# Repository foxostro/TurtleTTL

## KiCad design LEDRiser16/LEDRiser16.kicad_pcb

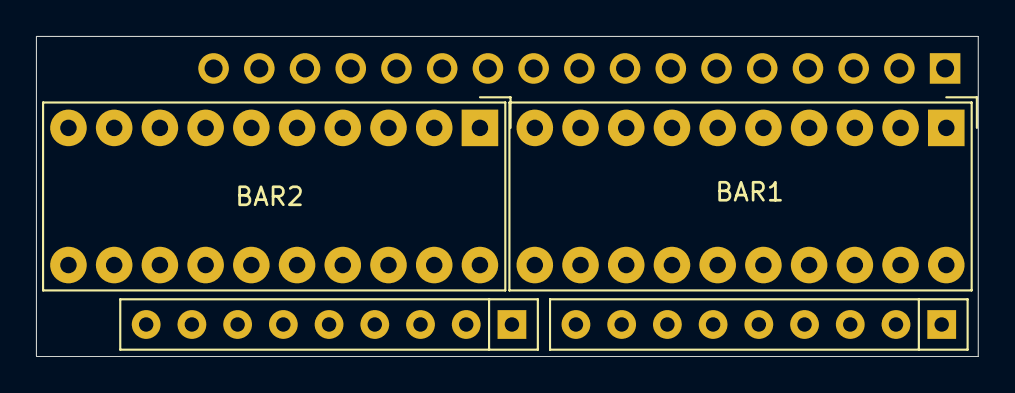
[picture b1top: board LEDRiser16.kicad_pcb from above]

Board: 2 copper layers, 52.3 x 17.8 mm, 5 parts (1 on the bottom side), 33 nets, no tracks yet.

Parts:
BAR1, BAR2: HDSP-4830_2; HDSP-4830
J1: Conn_01x17_Male; PinHeader_1x17_P2.54mm_Vertical
RN1, RN2: 10kΩ; R_Array_SIP9

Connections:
GND: J1.17, RN1.1, RN2.1
unnamed: BAR1.1, J1.1
unnamed: BAR1.2, J1.2
unnamed: BAR1.3, J1.3
unnamed: BAR1.4, J1.4
unnamed: BAR1.5, J1.5
unnamed: BAR1.6, J1.6
unnamed: BAR1.7, J1.7
unnamed: BAR1.8, J1.8
unnamed: BAR1.9, J1.9
unnamed: BAR1.10, J1.10
unnamed: BAR1.11, RN2.3
unnamed: BAR1.12, RN2.2
unnamed: BAR1.13, RN1.9
unnamed: BAR1.14, RN1.8
unnamed: BAR1.15, RN1.7
unnamed: BAR1.16, RN1.6
unnamed: BAR1.17, RN1.5
unnamed: BAR1.18, RN1.4
unnamed: BAR1.19, RN1.3
unnamed: BAR1.20, RN1.2
unnamed: BAR2.1, J1.11
unnamed: BAR2.2, J1.12
unnamed: BAR2.3, J1.13
unnamed: BAR2.4, J1.14
unnamed: BAR2.5, J1.15
unnamed: BAR2.6, J1.16
unnamed: BAR2.15, RN2.9
unnamed: BAR2.16, RN2.8
unnamed: BAR2.17, RN2.7
unnamed: BAR2.18, RN2.6
unnamed: BAR2.19, RN2.5
unnamed: BAR2.20, RN2.4

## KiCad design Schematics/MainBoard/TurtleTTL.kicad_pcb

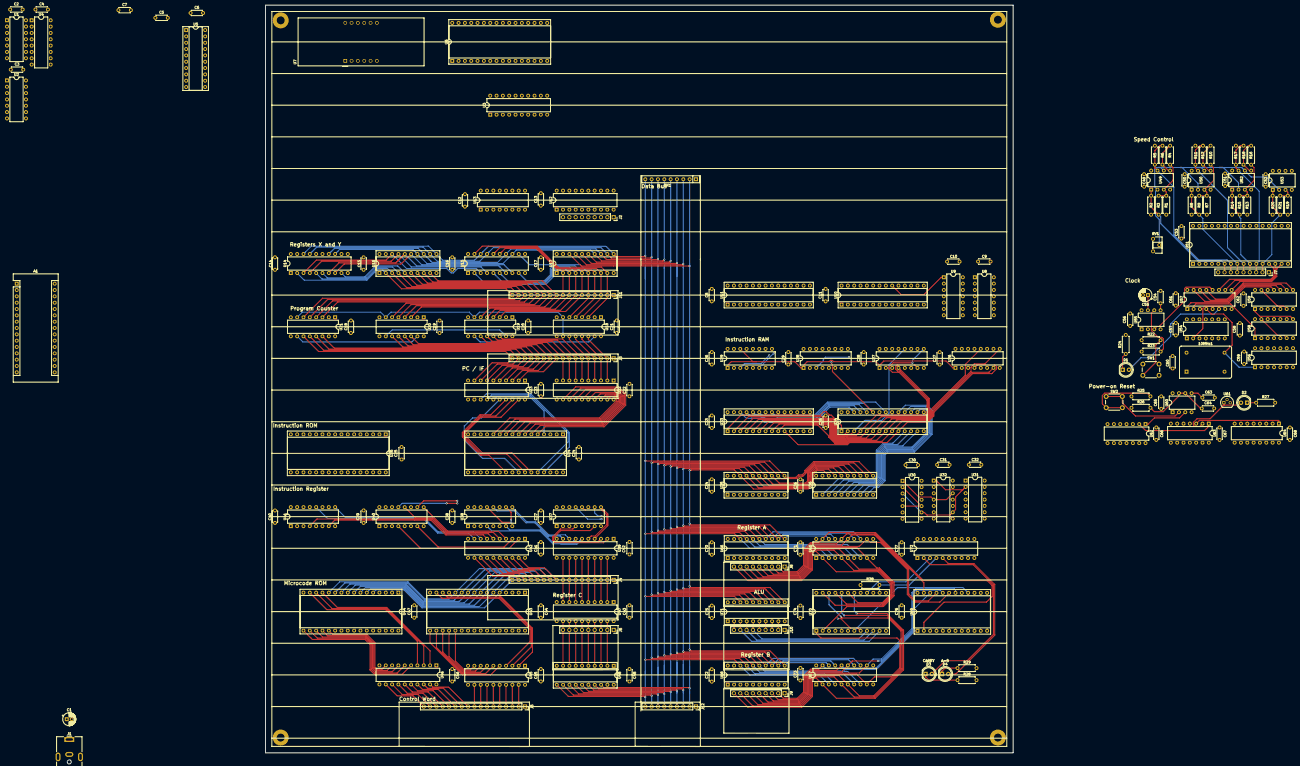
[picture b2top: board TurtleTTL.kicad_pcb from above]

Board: 6 copper layers, 300.0 x 300.0 mm, 204 parts (0 on the bottom side), 305 nets.

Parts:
10MHz1: ACO-xxxMHz; Oscillator_DIP-14
A1: Arduino_Nano_v3.x; Arduino_Nano
C1, C55: 10µF; CP_Radial_D5.0mm_P2.00mm
C2, C3, C4, C5, C6, C7, C8, C9, C10, C11, C12, C13, C14, C15, C16, C17, C18, C19, C20, C21, C22, C23, C24, C25, C26, C27, C28, C29, C30, C31, C32, C33, C34, C35, C36, C37, C38, C39, C40, C41, C42, C43, C44, C45, C46, C47, C48, C49, C50, C51, C52, C53, C56, C57, C58, C59, C60, C61, C62, C64, C65, C66, C67, C68, C70, C71, C72, C73, C74, C75, C76, C77: 100nF; C_Disc_D4.3mm_W1.9mm_P5.00mm
C54, C63: 10nF; C_Disc_D4.3mm_W1.9mm_P5.00mm
D1, D2, D3, D4: LED; LED_D5.0mm
J1: Barrel_Jack; BarrelJack_CUI_PJ-063AH_Horizontal
J2: Device Select LED Connector; PinSocket_1x09_P2.54mm_Vertical
J3: Program Counter LED Connector; PinSocket_1x17_P2.54mm_Vertical
J4: Instruction Register LED Connector; PinSocket_1x17_P2.54mm_Vertical
J5: C Register LED Connector; PinSocket_1x09_P2.54mm_Vertical
J6: Control Word LED Connector; PinSocket_1x17_P2.54mm_Vertical
J7: Speed Control LED Connector; PinSocket_1x09_P2.54mm_Vertical
J8: A Register LED Connector; PinSocket_1x09_P2.54mm_Vertical
J9: B Register LED Connector; PinSocket_1x09_P2.54mm_Vertical
J10: ALU Result LED Connector; PinSocket_1x09_P2.54mm_Vertical
J11: Address Bus LED Connector; PinSocket_1x17_P2.54mm_Vertical
J12: Data Bus LED Connector; PinSocket_1x09_P2.54mm_Vertical
MOUNT_LL: MountingHole_3.2mm_M3_Pad
MOUNT_LR: MountingHole_3.2mm_M3_Pad
MOUNT_UL: MountingHole_3.2mm_M3_Pad
MOUNT_UR: MountingHole_3.2mm_M3_Pad
R1, R2, R4, R5, R7, R8, R10, R11, R13, R14, R16, R17, R19, R20: 1k; R_Axial_DIN0207_L6.3mm_D2.5mm_P7.62mm_Horizontal
R3, R6, R9, R12, R15, R18, R21: 4.7k; R_Axial_DIN0207_L6.3mm_D2.5mm_P7.62mm_Horizontal
R22, R24, R27, R28, R29: 220Ω; R_Axial_DIN0207_L6.3mm_D2.5mm_P7.62mm_Horizontal
R23: 47kΩ; R_Axial_DIN0207_L6.3mm_D2.5mm_P7.62mm_Horizontal
R25: 1kΩ; R_Axial_DIN0207_L6.3mm_D2.5mm_P7.62mm_Horizontal
R26: 1MΩ; R_Axial_DIN0207_L6.3mm_D2.5mm_P7.62mm_Horizontal
R38: 4.7kΩ; R_Axial_DIN0207_L6.3mm_D2.5mm_P7.62mm_Horizontal
RN1: 1kΩ; R_Array_SIP9
RV1: R_POT; Potentiometer_ACP_CA6-H2,5_Horizontal
SW1: Step; SW_PUSH_6mm_H5mm
SW2: Reset; SW_PUSH_6mm_H5mm
U1, U56, U58, U59: 74LS393; DIP-14_W7.62mm
U2, U8, U32: 74LS32; DIP-14_W7.62mm
U3, U12, U14, U15, U65, U67, U72: 74F377; DIP-20_W7.62mm
U4: 74LS139; DIP-16_W7.62mm
U5, U16, U17, U35, U36, U48, U66, U68, U71: 74LS245; DIP-20_W7.62mm_Socket
U6, U24, U25, U43, U44, U51: GLS29EE010; DIP-32_W15.24mm_Socket
U7: CC56-12CGKWA; CA56-12CGKWA
U9, U31, U54, U62: 74LS04; DIP-14_W7.62mm
U10, U11, U33, U34: IDT71256SA12TPG; DIP-28_W7.62mm_Socket
U13: 74LS138; DIP-16_W7.62mm
U18, U19, U20, U21: 74F161; DIP-16_W7.62mm
U22, U23, U39, U42, U45, U46, U47: 74F574; DIP-20_W7.62mm
U26, U27, U28, U29, U37, U38, U40, U41: 74F157; DIP-16_W7.62mm
U30, U63: 74LS08; DIP-14_W7.62mm
U49, U50, U52, U53: LM393; DIP-8_W7.62mm
U55, U60: LM555; DIP-8_W7.62mm
U57: 74LS151; DIP-16_W7.62mm
U61: MCP100-450D; TO-92
U64: 74LS157; DIP-16_W7.62mm
U69, U70: 74F181; DIP-24_W15.24mm_Socket

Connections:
/ALU/A=B: R38.2, U69.14, U70.14, U72.4
/ALU/AluResult0: J10.2, U69.9, U71.9
/ALU/AluResult1: J10.3, U69.10, U71.8
/ALU/AluResult2: J10.4, U69.11, U71.7
/ALU/AluResult3: J10.5, U69.13, U71.6
/ALU/AluResult4: J10.6, U70.9, U71.5
/ALU/AluResult5: J10.7, U70.10, U71.4
/ALU/AluResult6: J10.8, U70.11, U71.3
/ALU/AluResult7: J10.9, U70.13, U71.2
/ALU/Cn+4: U70.16, U72.3
/Output Display/Out0: U3.2, U5.2, U6.12
/Output Display/Out1: U3.5, U5.3, U6.11
/Output Display/Out2: U3.6, U5.4, U6.10
/Output Display/Out3: U3.9, U5.5, U6.9
/Output Display/Out4: U3.12, U5.6, U6.8
/Output Display/Out5: U3.15, U5.7, U6.7
/Output Display/Out6: U3.16, U5.8, U6.6
/Output Display/Out7: U3.19, U5.9, U6.5
A0: J8.2, U65.19, U66.9, U69.2
A1: J8.3, U65.16, U66.8, U69.23
A2: J8.4, U65.15, U66.7, U69.21
A3: J8.5, U65.12, U66.6, U69.19
A4: J8.6, U65.9, U66.5, U70.2
A5: J8.7, U65.6, U66.4, U70.23
A6: J8.8, U65.5, U66.3, U70.21
A7: J8.9, U65.2, U66.2, U70.19
AddressBus0: A1.16, J11.2, U10.10, U11.10, U15.19, U17.9, U18.3, U26.3
AddressBus1: J11.3, U10.9, U11.9, U15.16, U17.8, U18.4, U26.6
AddressBus2: J11.4, U10.8, U11.8, U15.15, U17.7, U18.5, U26.10
AddressBus3: J11.5, U10.7, U11.7, U15.12, U17.6, U18.6, U26.13
AddressBus4: J11.6, U10.6, U11.6, U15.9, U17.5, U19.3, U27.3
AddressBus5: J11.7, U10.5, U11.5, U15.6, U17.4, U19.4, U27.6
AddressBus6: J11.8, U10.4, U11.4, U15.5, U17.3, U19.5, U27.10
AddressBus7: J11.9, U10.3, U11.3, U15.2, U17.2, U19.6, U27.13
AddressBus8: J11.10, U10.25, U11.25, U14.19, U16.9, U20.3, U28.3
AddressBus9: J11.11, U10.24, U11.24, U14.16, U16.8, U20.4, U28.6
AddressBus10: J11.12, U10.21, U11.21, U14.15, U16.7, U20.5, U28.10
AddressBus11: J11.13, U10.23, U11.23, U14.12, U16.6, U20.6, U28.13
AddressBus12: J11.14, U10.2, U11.2, U14.9, U16.5, U21.3, U29.3
AddressBus13: J11.15, U10.26, U11.26, U14.6, U16.4, U21.4, U29.6
AddressBus14: J11.16, U10.1, U11.1, U14.5, U16.3, U21.5, U29.10
AddressBus15: J11.17, U9.1, U10.20, U14.2, U16.2, U21.6, U29.13
B0: J9.2, U67.19, U68.9, U69.1
B1: J9.3, U67.16, U68.8, U69.22
B2: J9.4, U67.15, U68.7, U69.20
B3: J9.5, U67.12, U68.6, U69.18
B4: J9.6, U67.9, U68.5, U70.1
B5: J9.7, U67.6, U68.4, U70.22
B6: J9.8, U67.5, U68.3, U70.20
B7: J9.9, U67.2, U68.2, U70.18
C0: J5.2, U47.19, U48.2, U69.6, U70.6
C1: J5.3, U47.18, U48.3, U69.5, U70.5
C2: J5.4, U47.17, U48.4, U69.4, U70.4
C3: J5.5, U47.16, U48.5, U69.3, U70.3
C4: J5.6, U47.15, U48.6, U69.7
C5: J5.7, U47.14, U48.7, U69.8, U70.8
C6: J5.8, U47.13, U48.8
C7: J5.9, U47.12, U48.9
CE: U18.7, U18.10, U19.7, U20.7, U21.7
CLK: U57.5, U64.3
ClockRate0: U51.13, U57.11
ClockRate1: U51.14, U57.10
ClockRate2: U51.15, U57.9
ControlClock: U18.2, U19.2, U20.2, U21.2, U22.11, U23.11, U39.11, U42.11, U45.11, U46.11, U47.11, U64.4
DataBus0: A1.7, J12.2, RN1.2, U3.3, U5.18, U10.11, U11.11, U12.3, U14.3, U15.3, U16.18, U17.18, U35.18, U36.18, U48.18, U65.18, U66.11, U67.18, U68.11, U71.11
DataBus1: A1.8, J12.3, RN1.3, U3.4, U5.17, U10.12, U11.12, U12.4, U14.4, U15.4, U16.17, U17.17, U35.17, U36.17, U48.17, U65.17, U66.12, U67.17, U68.12, U71.12
DataBus2: A1.9, J12.4, RN1.4, U3.7, U5.16, U10.13, U11.13, U12.7, U14.7, U15.7, U16.16, U17.16, U35.16, U36.16, U48.16, U65.14, U66.13, U67.14, U68.13, U71.13
DataBus3: A1.10, J12.5, RN1.5, U3.8, U5.15, U10.15, U11.15, U12.8, U14.8, U15.8, U16.15, U17.15, U35.15, U36.15, U48.15, U65.13, U66.14, U67.13, U68.14, U71.14
DataBus4: A1.11, J12.6, RN1.6, U3.13, U5.14, U10.16, U11.16, U12.13, U14.13, U15.13, U16.14, U17.14, U35.14, U36.14, U48.14, U65.8, U66.15, U67.8, U68.15, U71.15
DataBus5: A1.12, J12.7, RN1.7, U3.14, U5.13, U10.17, U11.17, U12.14, U14.14, U15.14, U16.13, U17.13, U35.13, U36.13, U48.13, U65.7, U66.16, U67.7, U68.16, U71.16
DataBus6: A1.13, J12.8, RN1.8, U3.17, U5.12, U10.18, U11.18, U12.17, U14.17, U15.17, U16.12, U17.12, U35.12, U36.12, U48.12, U65.4, U66.17, U67.4, U68.17, U71.17
DataBus7: A1.14, J12.9, RN1.9, U3.18, U5.11, U10.19, U11.19, U12.18, U14.18, U15.18, U16.11, U17.11, U35.11, U36.11, U48.11, U65.3, U66.18, U67.3, U68.18, U71.18
DeviceSelect0: J2.2, U13.15
DeviceSelect1: J2.3, U2.2, U2.4, U13.14
DeviceSelect2: J2.4, U13.13
DeviceSelect3: J2.5, U13.12, U31.1, U32.2, U32.5
DeviceSelect4: J2.6, U13.11, U31.3, U32.10, U32.13
DeviceSelect5: J2.7, U8.2, U8.4, U13.10
DeviceSelect6: J2.8, U13.9
DeviceSelect7: J2.9, U13.7
FixedRateClock: U1.1, U56.6, U56.13, U57.3, U64.2
GND: 10MHz1.7, A1.4, A1.29, C1.2, C2.2, C3.2, C4.2, C5.2, C6.2, C7.2, C8.2, C9.2, C10.2, C11.2, C12.2, C13.2, C14.2, C15.2, C16.2, C17.2, C18.2, C19.2, C20.2, C21.2, C22.2, C23.2, C24.2, C25.2, C26.2, C27.2, C28.2, C29.2, C30.2, C31.2, C32.2, C33.2, C34.2, C35.2, C36.2, C37.2, C38.2, C39.2, C40.2, C41.2, C42.2, C43.2, C44.2, C45.2, C46.2, C47.2, C48.2, C49.2, C50.2, C51.2, C52.2, C53.2, C54.2, C55.2, C56.2, C57.2, C58.2, C59.2, C60.2, C61.2, C62.2, C63.2, C64.2, C65.2, C66.2, C67.2, C68.2, C70.2, C71.2, C72.2, C73.2, C74.2, C75.2, C76.2, C77.2, J1.2, J2.1, J3.1, J4.1, J5.1, J6.1, J7.1, J8.1, J9.1, J10.1, J11.1, J12.1, R1.1, R24.2, R27.2, R28.2, R29.2, RN1.1, RV1.3, U1.2, U3.10, U4.1, U5.10, U6.2, U6.3, U6.4, U6.16, U6.22, U6.23, U6.24, U6.25, U6.26, U6.27, U6.28, U6.29, U10.14, U11.14, U12.10, U13.4, U13.5, U13.8, U14.10, U15.10, U16.10, U17.10, U18.8, U19.8, U20.8, U21.8, U22.1, U22.10, U23.1, U23.10, U24.2, U24.16, U24.22, U24.24, U25.2, U25.16, U25.22, U25.24, U26.8, U26.15, U27.8, U27.15, U28.8, U28.15, U29.8, U29.15, U33.14, U33.20, U34.14, U34.20, U35.10, U36.10, U37.8, U37.15, U38.8, U38.15, U39.1, U39.10, U40.8, U40.15, U41.8, U41.15, U42.1, U42.10, U43.2, U43.3, U43.4, U43.16, U43.22, U43.23, U43.24, U43.25, U43.28, U43.29, U44.2, U44.3, U44.4, U44.16, U44.22, U44.23, U44.24, U44.25, U44.28, U44.29, U45.1, U45.10, U46.1, U46.10, U47.1, U47.10, U48.10, U51.2, U51.3, U51.4, U51.5, U51.16, U51.17, U51.18, U51.19, U51.20, U51.21, U51.22, U51.23, U51.24, U51.25, U51.26, U51.27, U51.28, U51.29, U55.1, U56.2, U56.12, U57.8, U58.2, U58.12, U59.2, U59.12, U60.1, U61.3, U64.5, U64.6, U64.7, U64.8, U64.9, U64.10, U64.11, U64.12, U64.13, U64.14, U64.15, U65.10, U66.10, U67.10, U68.10, U69.12, U70.12, U71.10, U72.10
IR0: J4.2, U39.19, U47.2
IR1: J4.3, U39.18, U47.3
IR2: J4.4, U39.17, U47.4
IR3: J4.5, U39.16, U47.5
IR4: J4.6, U39.15, U47.6
IR5: J4.7, U39.14, U47.7
IR6: J4.8, U39.13, U47.8
IR7: J4.9, U39.12, U47.9
IR8: J4.10, U42.19, U43.12, U44.12
IR9: J4.11, U42.18, U43.11, U44.11
IR10: J4.12, U42.17, U43.10, U44.10
IR11: J4.13, U42.16, U43.9, U44.9
IR12: J4.14, U42.15, U43.8, U44.8
IR13: J4.15, U42.14, U43.7, U44.7
IR14: J4.16, U42.13, U43.6, U44.6
IR15: J4.17, U42.12, U43.5, U44.5
IRAM0: U34.11, U36.2, U37.3
IRAM1: U34.12, U36.3, U37.6
IRAM2: U34.13, U36.4, U37.10
IRAM3: U34.15, U36.5, U37.13
IRAM4: U34.16, U36.6, U38.3
IRAM5: U34.17, U36.7, U38.6
IRAM6: U34.18, U36.8, U38.10
IRAM7: U34.19, U36.9, U38.13
IRAM8: U33.11, U35.2, U40.3
IRAM9: U33.12, U35.3, U40.6
IRAM10: U33.13, U35.4, U40.10
IRAM11: U33.15, U35.5, U40.13
IRAM12: U33.16, U35.6, U41.3
IRAM13: U33.17, U35.7, U41.6
IRAM14: U33.18, U35.8, U41.10
IRAM15: U33.19, U35.9, U41.13
IRAMAddr0: U26.4, U33.10, U34.10
IRAMAddr1: U26.7, U33.9, U34.9
IRAMAddr2: U26.9, U33.8, U34.8
IRAMAddr3: U26.12, U33.7, U34.7
IRAMAddr4: U27.4, U33.6, U34.6
IRAMAddr5: U27.7, U33.5, U34.5
IRAMAddr6: U27.9, U33.4, U34.4
IRAMAddr7: U27.12, U33.3, U34.3
IRAMAddr8: U28.4, U33.25, U34.25
IRAMAddr9: U28.7, U33.24, U34.24
IRAMAddr10: U28.9, U33.21, U34.21
IRAMAddr11: U28.12, U33.23, U34.23
IRAMAddr12: U29.4, U33.2, U34.2
IRAMAddr13: U29.7, U33.26, U34.26
IRAMAddr14: U29.9, U33.1, U34.1
IROM0: U24.13, U37.2
IROM1: U24.14, U37.5
IROM2: U24.15, U37.11
IROM3: U24.17, U37.14
IROM4: U24.18, U38.2
IROM5: U24.19, U38.5
IROM6: U24.20, U38.11
IROM7: U24.21, U38.14
IROM8: U25.13, U40.2
IROM9: U25.14, U40.5
IROM10: U25.15, U40.11
IROM11: U25.17, U40.14
IROM12: U25.18, U41.2
IROM13: U25.19, U41.5
IROM14: U25.20, U41.11
IROM15: U25.21, U41.14
unnamed: 10MHz1.8, U56.1, U57.4
unnamed: C54.1, U55.5
unnamed: C55.1, R23.2, U55.6, U55.7
unnamed: C63.1, U60.5
unnamed: C64.1, R26.2, U60.6, U60.7
unnamed: D1.1, R24.1
unnamed: D2.1, R27.1
unnamed: D2.2, U61.1, U63.2
unnamed: D3.1, R28.1
unnamed: D4.1, R29.1
unnamed: J7.2, R20.1, R21.1, U51.12, U53.1
unnamed: J7.3, R17.1, R18.1, U51.11, U52.7
unnamed: J7.4, R14.1, R15.1, U51.10, U52.1
unnamed: J7.5, R11.1, R12.1, U50.7, U51.9
unnamed: J7.6, R8.1, R9.1, U50.1, U51.8
unnamed: J7.7, R5.1, R6.1, U49.7, U51.7
unnamed: J7.8, R2.1, R3.1, U49.1, U51.6
unnamed: R1.2, R3.2, R4.1, U49.3
unnamed: R4.2, R6.2, R7.1, U49.5
unnamed: R7.2, R9.2, R10.1, U50.3
unnamed: R10.2, R12.2, R13.1, U50.5
unnamed: R13.2, R15.2, R16.1, U52.3
unnamed: R16.2, R18.2, R19.1, U52.5
unnamed: R19.2, R21.2, U53.3
unnamed: R22.2, SW1.2
unnamed: R25.2, SW2.2
unnamed: RV1.2, U49.2, U49.6, U50.2, U50.6, U52.2, U52.6, U53.2
unnamed: SW1.1, U55.2
unnamed: SW2.1, U60.2
unnamed: U1.3, U4.2
unnamed: U1.4, U4.3
unnamed: U2.3, U3.1
unnamed: U2.6, U5.19
unnamed: U4.4, U7.6
unnamed: U4.5, U7.8
unnamed: U4.6, U7.9
unnamed: U4.7, U7.12
unnamed: U6.13, U7.5
unnamed: U6.14, U7.10
unnamed: U6.15, U7.1
unnamed: U6.17, U7.2
unnamed: U6.18, U7.4
unnamed: U6.19, U7.7
unnamed: U6.20, U7.11
unnamed: U6.21, U7.3
unnamed: U8.6, U10.22, U11.22
unnamed: U8.3, U10.27, U11.27
unnamed: U9.2, U11.20
unnamed: U12.2, U13.1
unnamed: U12.5, U13.2
unnamed: U12.6, U13.3
unnamed: U18.15, U19.10
unnamed: U19.15, U20.10
unnamed: U20.15, U21.10
unnamed: U30.3, U30.9, U31.2, U32.1, U32.9
unnamed: U30.4, U31.4
unnamed: U30.6, U34.22
unnamed: U30.8, U33.22
unnamed: U32.3, U35.19
unnamed: U32.6, U33.27
unnamed: U32.8, U36.19
unnamed: U32.11, U34.27
unnamed: U37.4, U39.2
unnamed: U37.7, U39.3
unnamed: U37.9, U39.4
unnamed: U37.12, U39.5
unnamed: U38.4, U39.6
unnamed: U38.7, U39.7
unnamed: U38.9, U39.8
unnamed: U38.12, U39.9
unnamed: U40.4, U42.2
unnamed: U40.7, U42.3
unnamed: U40.9, U42.4
unnamed: U40.12, U42.5
unnamed: U41.4, U42.6
unnamed: U41.7, U42.7
unnamed: U41.9, U42.8
unnamed: U41.12, U42.9
unnamed: U43.13, U45.2
unnamed: U43.14, U45.3
unnamed: U43.15, U45.4
unnamed: U43.17, U45.5
unnamed: U43.18, U45.6
unnamed: U43.19, U45.7
unnamed: U43.20, U45.8
unnamed: U43.21, U45.9
unnamed: U44.13, U46.2
unnamed: U44.14, U46.3
unnamed: U44.15, U46.4
unnamed: U44.17, U46.5
unnamed: U44.18, U46.6
unnamed: U44.19, U46.7
unnamed: U44.20, U46.8
unnamed: U44.21, U46.9
unnamed: U54.2, U57.7
unnamed: U55.3, U57.12
unnamed: U56.8, U57.2, U58.1
unnamed: U57.1, U59.11
unnamed: U57.13, U59.8
unnamed: U57.14, U59.9
unnamed: U57.15, U59.10
unnamed: U58.8, U59.1
unnamed: U58.6, U58.13
unnamed: U59.6, U59.13
unnamed: U60.3, U62.1
unnamed: U62.2, U63.1
unnamed: U69.16, U70.7
PC0: J3.2, U18.14, U22.2
PC1: J3.3, U18.13, U22.3
PC2: J3.4, U18.12, U22.4
PC3: J3.5, U18.11, U22.5
PC4: J3.6, U19.14, U22.6
PC5: J3.7, U19.13, U22.7
PC6: J3.8, U19.12, U22.8
PC7: J3.9, U19.11, U22.9
PC8: J3.10, U20.14, U23.2
PC9: J3.11, U20.13, U23.3
PC10: J3.12, U20.12, U23.4
PC11: J3.13, U20.11, U23.5
PC12: J3.14, U21.14, U23.6
PC13: J3.15, U21.13, U23.7
PC14: J3.16, U21.12, U23.8
PC15: J3.17, U21.11, U23.9, U37.1, U38.1, U40.1, U41.1
PC_IF0: U22.19, U24.12, U25.12, U26.2
PC_IF1: U22.18, U24.11, U25.11, U26.5
PC_IF2: U22.17, U24.10, U25.10, U26.11
PC_IF3: U22.16, U24.9, U25.9, U26.14
PC_IF4: U22.15, U24.8, U25.8, U27.2
PC_IF5: U22.14, U24.7, U25.7, U27.5
PC_IF6: U22.13, U24.6, U25.6, U27.11
PC_IF7: U22.12, U24.5, U25.5, U27.14
PC_IF8: U23.19, U24.27, U25.27, U28.2
PC_IF9: U23.18, U24.26, U25.26, U28.5
PC_IF10: U23.17, U24.23, U25.23, U28.11
PC_IF11: U23.16, U24.25, U25.25, U28.14
PC_IF12: U23.15, U24.4, U25.4, U29.2
PC_IF13: U23.14, U24.28, U25.28, U29.5
PC_IF14: U23.13, U24.29, U25.29, U29.11
PC_IF15: U23.12, U24.3, U25.3, U26.1, U27.1, U28.1, U29.1, U29.14
RegisterClock: A1.19, D1.2, U3.11, U12.11, U14.11, U15.11, U57.6, U65.11, U67.11, U72.11
VCC: 10MHz1.14, A1.30, C1.1, C2.1, C3.1, C4.1, C5.1, C6.1, C7.1, C8.1, C9.1, C10.1, C11.1, C12.1, C13.1, C14.1, C15.1, C16.1, C17.1, C18.1, C19.1, C20.1, C21.1, C22.1, C23.1, C24.1, C25.1, C26.1, C27.1, C28.1, C29.1, C30.1, C31.1, C32.1, C33.1, C34.1, C35.1, C36.1, C37.1, C38.1, C39.1, C40.1, C41.1, C42.1, C43.1, C44.1, C45.1, C46.1, C47.1, C48.1, C49.1, C50.1, C51.1, C52.1, C53.1, C56.1, C57.1, C58.1, C59.1, C60.1, C61.1, C62.1, C65.1, C66.1, C67.1, C68.1, C70.1, C71.1, C72.1, C73.1, C74.1, C75.1, C76.1, C77.1, J1.1, R2.2, R5.2, R8.2, R11.2, R14.2, R17.2, R20.2, R22.1, R23.1, R25.1, R26.1, R38.1, RV1.1, U1.5, U1.6, U3.20, U5.1, U5.20, U6.31, U6.32, U10.28, U11.28, U12.20, U13.6, U13.16, U14.20, U15.20, U16.1, U16.20, U17.1, U17.20, U18.16, U19.16, U20.16, U21.15, U21.16, U22.20, U23.20, U24.31, U24.32, U25.31, U25.32, U26.16, U27.16, U28.16, U29.16, U33.28, U34.28, U35.20, U36.20, U37.16, U38.16, U39.20, U40.16, U41.16, U42.20, U43.31, U43.32, U44.31, U44.32, U45.20, U46.20, U47.20, U48.1, U48.20, U51.31, U51.32, U55.4, U55.8, U56.3, U56.4, U56.5, U56.9, U56.10, U56.11, U57.16, U58.3, U58.4, U58.5, U58.9, U58.10, U58.11, U59.3, U59.4, U59.5, U60.4, U60.8, U61.2, U64.16, U65.20, U66.1, U66.20, U67.20, U68.1, U68.20, U69.24, U70.24, U71.1, U71.20, U72.20
~A=B: D4.2, U43.27, U44.27, U72.5
~AI: J6.13, U46.16, U65.1
~AO: J6.12, U46.17, U66.19
~BI: J6.15, U46.14, U67.1
~BO: J6.14, U46.15, U68.19
~CO: J6.2, U45.19, U48.19
~CarryOut: D3.2, U43.26, U44.26, U72.2
~DI: J6.16, U12.1, U46.13
~EO: J6.10, U46.19, U71.19
~FI: J6.11, U46.18, U72.1
~HLT: J6.17, U46.12, U54.1
~J: J6.3, U18.9, U19.9, U20.9, U21.9, U45.18
~MI: A1.6, J6.9, U2.1, U8.1, U30.1, U32.4, U32.12, U35.1, U36.1, U45.12
~MO: A1.5, J6.8, U2.5, U8.5, U30.2, U30.5, U30.10, U45.13
~RST: U18.1, U19.1, U20.1, U21.1, U63.3, U64.1
~XI: J6.5, U14.1, U45.16
~XO: J6.7, U16.19, U45.14
~YI: J6.4, U15.1, U45.17
~YO: J6.6, U17.19, U45.15

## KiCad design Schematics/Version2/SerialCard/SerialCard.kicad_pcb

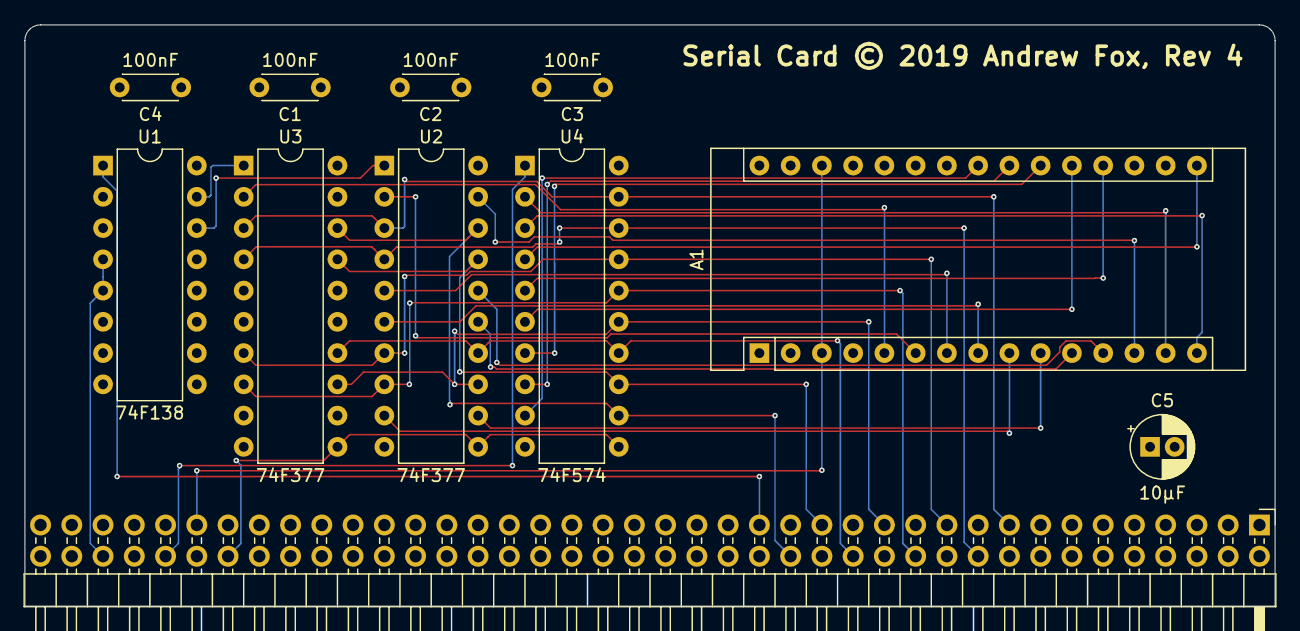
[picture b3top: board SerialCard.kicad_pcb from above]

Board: 4 copper layers, 101.6 x 47.2 mm, 11 parts (0 on the bottom side), 34 nets.

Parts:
A1: Arduino_Nano_v3.x; Arduino_Nano
C1, C2, C3, C4: 100nF; C_Disc_D4.3mm_W1.9mm_P5.00mm
C5: 10µF; CP_Radial_D5.0mm_P2.00mm
J1: Conn; PinHeader_2x40_P2.54mm_Horizontal
U1: 74F138; DIP-16_W7.62mm
U2, U3: 74F377; DIP-20_W7.62mm
U4: 74F574; DIP-20_W7.62mm

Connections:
AddressBus0: J1.33, U1.1
DataBus0: J1.17, U2.3, U3.3, U4.19
DataBus1: J1.20, U2.4, U3.4, U4.18
DataBus2: J1.21, U2.7, U3.7, U4.17
DataBus3: J1.24, U2.8, U3.8, U4.16
DataBus4: J1.25, U2.13, U3.13, U4.15
DataBus5: J1.28, U2.14, U3.14, U4.14
DataBus6: J1.29, U2.17, U3.17, U4.13
DataBus7: J1.32, U2.18, U3.18, U4.12
GND: A1.4, A1.29, C1.2, C2.2, C3.2, C4.2, C5.2, J1.2, J1.3, J1.6, J1.7, J1.10, J1.11, J1.14, J1.15, J1.18, J1.19, J1.22, J1.23, J1.26, J1.27, J1.30, J1.31, J1.34, J1.35, J1.38, J1.39, J1.42, J1.43, J1.46, J1.47, J1.50, J1.51, J1.54, J1.55, J1.58, J1.59, J1.62, J1.63, J1.66, J1.67, J1.70, J1.71, J1.74, J1.75, J1.78, J1.79, U1.2, U1.3, U1.8, U2.10, U3.10, U4.10
unnamed: A1.5, U3.2
unnamed: A1.6, U2.2
unnamed: A1.7, U2.5
unnamed: A1.8, U2.6
unnamed: A1.9, U2.9
unnamed: A1.10, U2.12
unnamed: A1.11, U2.15
unnamed: A1.12, U2.16
unnamed: A1.13, U2.19
unnamed: A1.14, U4.2
unnamed: A1.15, U4.3
unnamed: A1.16, U4.4
unnamed: A1.19, U4.5
unnamed: A1.20, U4.6
unnamed: A1.21, U4.7
unnamed: A1.22, U4.8
unnamed: A1.23, U4.9
unnamed: U1.14, U2.1
unnamed: U1.15, U3.1
RegisterClock: J1.68, U2.11, U3.11, U4.11
VCC: C1.1, C2.1, C3.1, C4.1, C5.1, J1.1, J1.4, J1.5, J1.8, J1.9, J1.12, J1.13, J1.16, J1.73, J1.77, J1.80, U1.6, U1.16, U2.20, U3.20, U4.20
~PI: J1.76, U1.4, U1.5
~PO: J1.72, U4.1
~RST: A1.3, A1.28, J1.69

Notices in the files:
Schematics/Version2/SerialCard/SerialCard.kicad_pcb:
Serial Card © 2019 Andrew Fox, Rev 4
